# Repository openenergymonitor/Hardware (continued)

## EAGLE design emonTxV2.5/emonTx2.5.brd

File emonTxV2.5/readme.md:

## EmonTx v2.5 Through Hole

**Update: This design was never manufactured or tested**

***

Main features:

- 2x CT sensor inputs using higher quality 3.5mm jacks used on the EmonTx v3 and emontx shield
- 1x ACAC Voltage sensing and power input
- Terminal block power, ADC's and Digital IO breakout + full spare IO breakout.
- Onboard DS18B20 footprint
- Based around ATmega328 + RFM69 core
- Fits in emonTH enclosure

### Eagle schematic and board file

Download both the schematic and board file and open in eagle, click on File > Switch to Board to navigate between schematic view and PCB Board view.

- Schematic: [emonTx2.5.sch](emonTx2.5.sch)
- Board: [emonTx2.5.brd](emonTx2.5.brd)

### Schematic

### Board

### Open Hardware

Hardware designs (schematics and CAD) files are licensed under the [Creative Commons Attribution-ShareAlike 3.0 Unported License](http://creativecommons.org/licenses/by-sa/3.0/) and follow the terms of the [OSHW (Open-source hardware) Statement of Principles 1.0.](http://freedomdefined.org/OSHW)

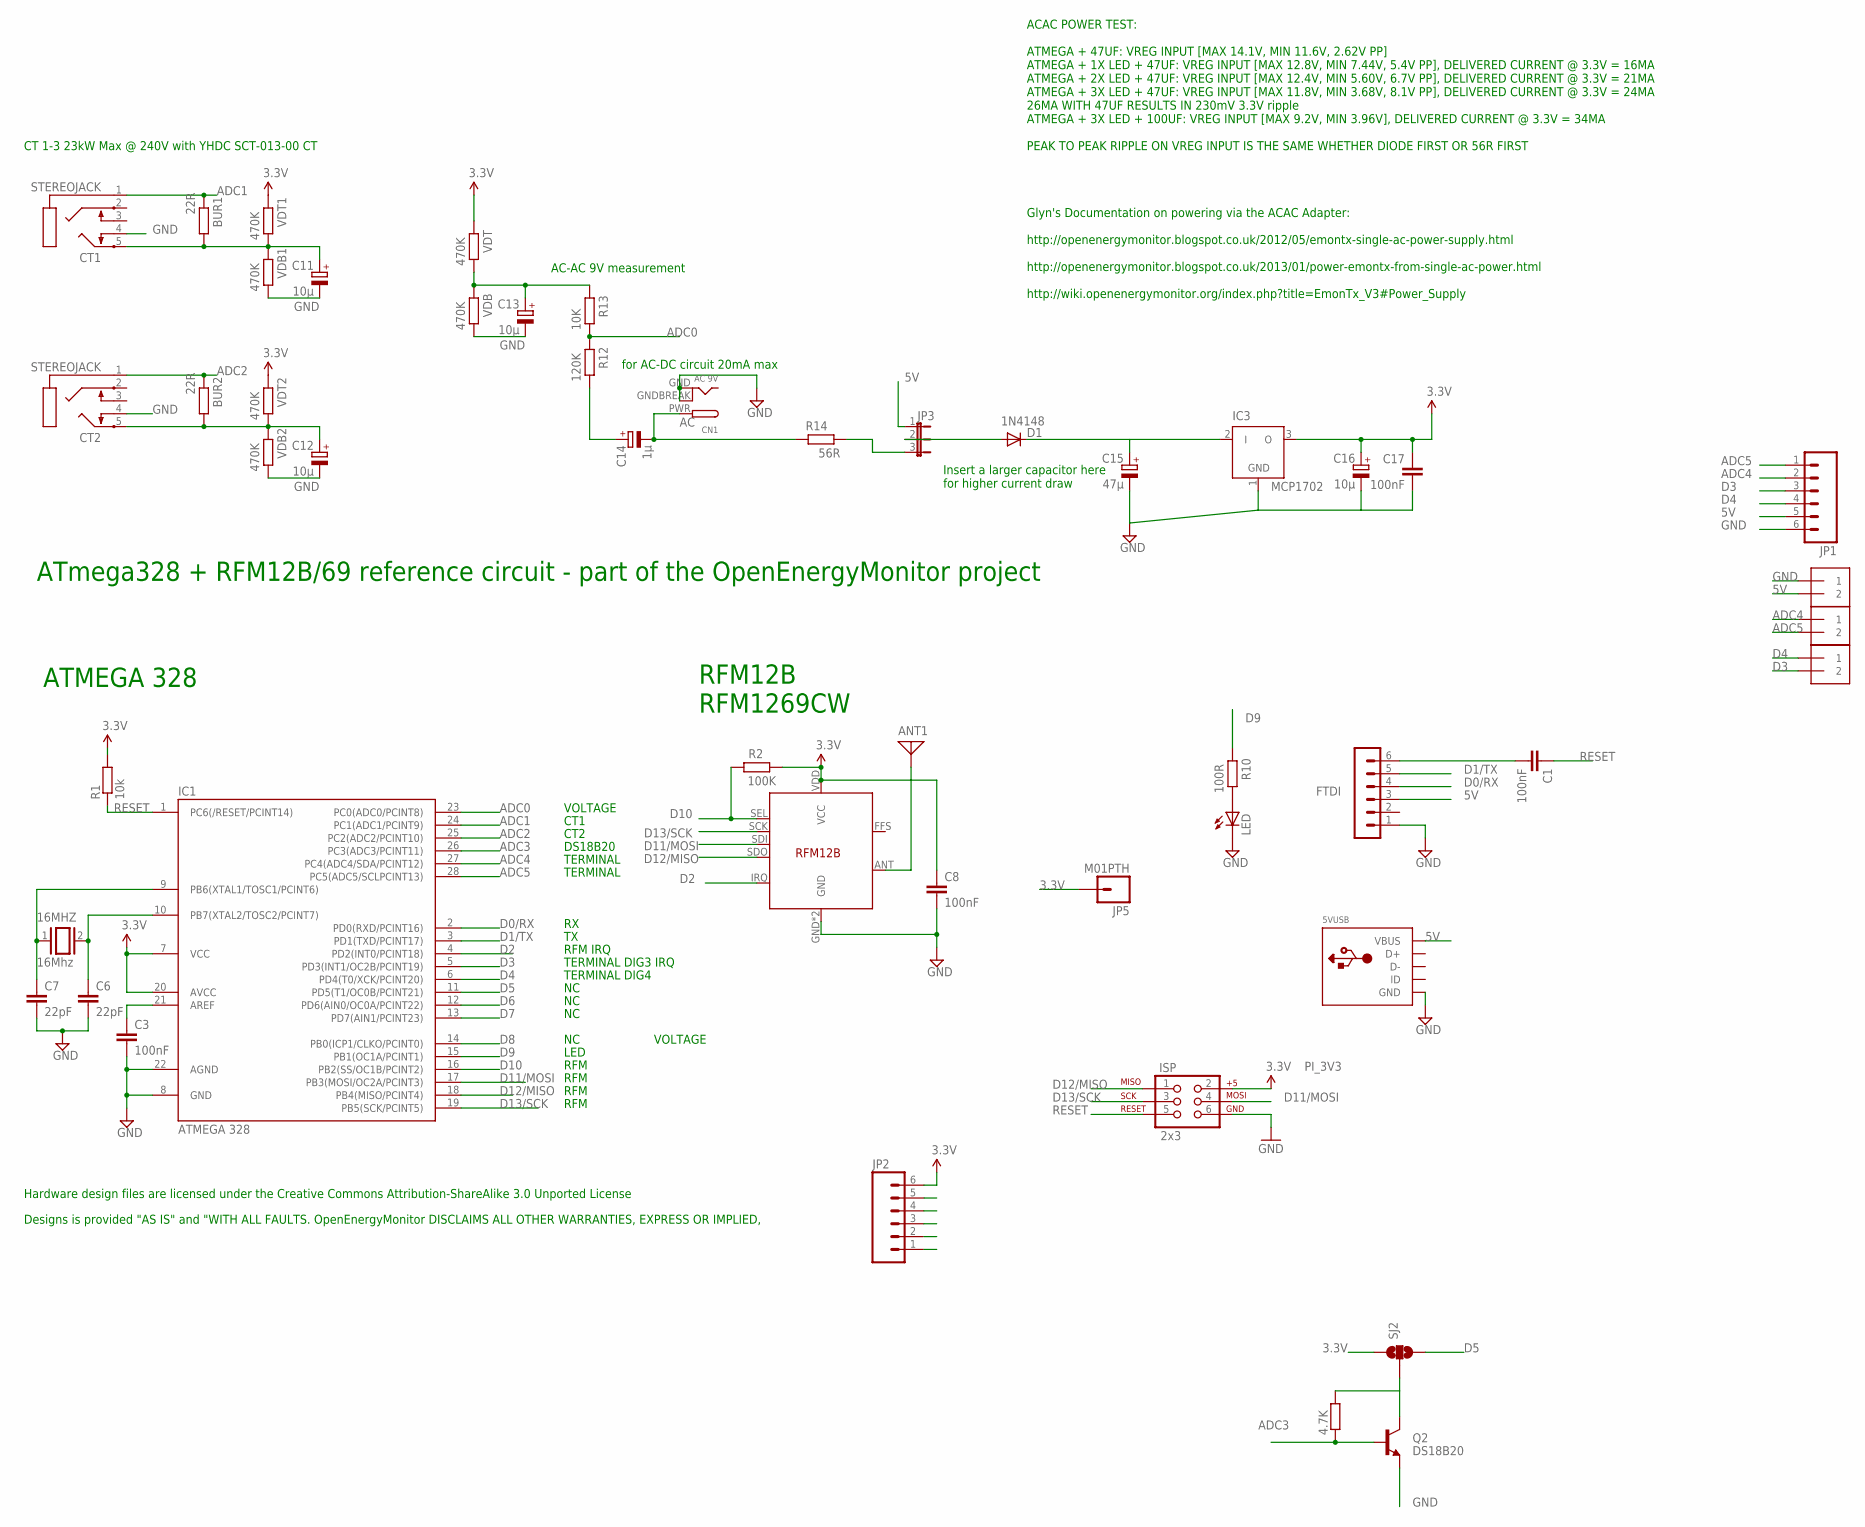
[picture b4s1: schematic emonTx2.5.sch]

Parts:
5VUSB: USBMOLEX; USB-MINIB-THM-MOLEX
16MHZ: 16Mhz; QS
ANT1: ANTENNA; PAD-01
BUR1, BUR2: 22R; 0204/7
C1, C3, C8, C17: 100nF; C025-024X044
C6, C7: 22pF; C2.5-2
C11, C12, C13, C16: 10µ; E1,8-4
C14: 1µ; E1,8-4
C15: 47µ; E1,8-4
CN1: AC 9V; DCJACK_2MM_PTH
CT1, CT2: STEREOJACK; STX3100
D1: 1N4148; DIODE-1N4148
FTDI: FTDI; MA06-1
IC1: ATMEGA 328; DIL28-3
IC3: MCP1702; TO92
ISP: 2x3; 2X3
J1, J2, J3: 1X2-3.5MM
JP1, JP2: M06SIP; 1X06
JP3: JP2E; JP2
JP5: M01PTH; 1X01
LED: LED3MM
Q2: DS18B20; TO-92
R1: 10k; 0204/7
R2: 100K; 0204/7
R9: 4.7K; 0204/7
R10: 100R; 0204/7
R12: 120K; 0204/7
R13: 10K; 0204/7
R14: 56R; 0204/7
SJ2: SOLDERJUMPER_2WAY-OLDS; SJ_3
U$14: RFM12B
VDB, VDB1, VDB2: 470K; 0204/7
VDT, VDT1, VDT2: 470K; 0204/7

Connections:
3.3V: C8.1, C16.+, C17.1, IC1.7 (VCC), IC1.20 (AVCC), IC3.3 (O), ISP.2, JP2.6, JP5.1, R1.2, R2.1, SJ2.1, U$14.VDD (VCC), VDT.2, VDT1.2, VDT2.2
5V: 5VUSB.VBUS, FTDI.3, J3.2, JP1.5, JP3.1
AC: C14.-, CN1.PWR, R14.2
ADC0: IC1.23 (PC0(ADC0/PCINT8)), R12.2, R13.1
ADC1: BUR1.2, CT1.1, IC1.24 (PC1(ADC1/PCINT9))
ADC2: BUR2.2, CT2.1, IC1.25 (PC2(ADC2/PCINT10))
ADC3: IC1.26 (PC3(ADC3/PCINT11)), Q2.2 (B), R9.2
ADC4: IC1.27 (PC4(ADC4/SDA/PCINT12)), J1.1, JP1.2
ADC5: IC1.28 (PC5(ADC5/SCLPCINT13)), J1.2, JP1.1
D0/RX: FTDI.4, IC1.2 (PD0(RXD/PCINT16))
D1/TX: FTDI.5, IC1.3 (PD1(TXD/PCINT17))
D2: IC1.4 (PD2(INT0/PCINT18)), U$14.IRQ
D3: IC1.5 (PD3(INT1/OC2B/PCINT19)), J2.2, JP1.3
D4: IC1.6 (PD4(T0/XCK/PCINT20)), J2.1, JP1.4
D5: IC1.11 (PD5(T1/OC0B/PCINT21)), JP2.2, SJ2.3
D6: IC1.12 (PD6(AIN0/OC0A/PCINT22)), JP2.3
D7: IC1.13 (PD7(AIN1/PCINT23)), JP2.4
D8: IC1.14 (PB0(ICP1/CLKO/PCINT0)), JP2.5
D9: IC1.15 (PB1(OC1A/PCINT1)), R10.2
D10: IC1.16 (PB2(SS/OC1B/PCINT2)), R2.2, U$14.SEL
D11/MOSI: IC1.17 (PB3(MOSI/OC2A/PCINT3)), ISP.4, U$14.SDI
D12/MISO: IC1.18 (PB4(MISO/PCINT4)), ISP.1, U$14.SDO
D13/SCK: IC1.19 (PB5(SCK/PCINT5)), ISP.3, U$14.SCK
DIG1: ANT1.1, U$14.ANT
GND: 5VUSB.GND, C3.2, C6.2, C7.2, C8.2, C11.-, C12.-, C13.-, C15.-, C16.-, C17.2, CN1.GND, CN1.GNDBREAK, CT1.4, CT2.4, FTDI.1, IC1.8 (GND), IC1.22 (AGND), IC3.1 (GND), ISP.6, J3.1, JP1.6, JP2.1, LED.K (C), Q2.1 (E), U$14.GND, U$14.P$12 (GND), VDB.1, VDB1.1, VDB2.1
unnamed: 16MHZ.2, C6.1, IC1.10 (PB7(XTAL2/TOSC2/PCINT7))
unnamed: BUR2.1, C12.+, CT2.5, VDB2.2, VDT2.1
unnamed: JP3.3, R14.1
unnamed: C15.+, D1.C, IC3.2 (I)
unnamed: D1.A, JP3.2
unnamed: C14.+, R12.1
unnamed: LED.A, R10.1
unnamed: Q2.3 (C), R9.1, SJ2.2
unnamed: 16MHZ.1, C7.1, IC1.9 (PB6(XTAL1/TOSC1/PCINT6))
unnamed: C1.2, FTDI.6
unnamed: C3.1, IC1.21 (AREF)
unnamed: C13.+, R13.2, VDB.2, VDT.1
unnamed: BUR1.1, C11.+, CT1.5, VDB1.2, VDT1.1
RESET: C1.1, IC1.1 (PC6(/RESET/PCINT14)), ISP.5, R1.1

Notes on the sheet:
RFM12B RFM1269CW
ATMEGA 328
Hardware design files are licensed under the Creative Commons Attribution-ShareAlike 3.0 Unported License
Designs is provided "AS IS" and "WITH ALL FAULTS. OpenEnergyMonitor DISCLAIMS ALL OTHER WARRANTIES, EXPRESS OR IMPLIED,
ATmega328 + RFM12B/69 reference circuit - part of the OpenEnergyMonitor project
CT 1-3 23kW Max @ 240V with YHDC SCT-013-00 CT
AC-AC 9V measurement
for AC-DC circuit 20mA max
Glyn's Documentation on powering via the ACAC Adapter: http://openenergymonitor.blogspot.co.uk/2012/05/emontx-single-ac-power-supply.html http://openenergymonitor.blogspot.co.uk/2013/01/power-emontx-from-single-ac-power.html http://wiki.openenergymonitor.org/index.php?title=EmonTx_V3#Power_Supply
ACAC POWER TEST: ATMEGA + 47UF: VREG INPUT [MAX 14.1V, MIN 11.6V, 2.62V PP] ATMEGA + 1X LED + 47UF: VREG INPUT [MAX 12.8V, MIN 7.44V, 5.4V PP], DELIVERED CURRENT @ 3.3V = 16MA ATMEGA + 2X LED + 47UF: VREG INPUT [MAX 12.4V, MIN 5.60V, 6.7V PP], DELIVERED CURRENT @ 3.3V = 21MA ATMEGA + 3X LED + 47UF: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
Insert a larger capacitor here for higher current draw
VOLTAGE
CT1
CT2
DS18B20
TERMINAL
RFM IRQ
TERMINAL DIG3 IRQ
TERMINAL DIG4
LED
RFM

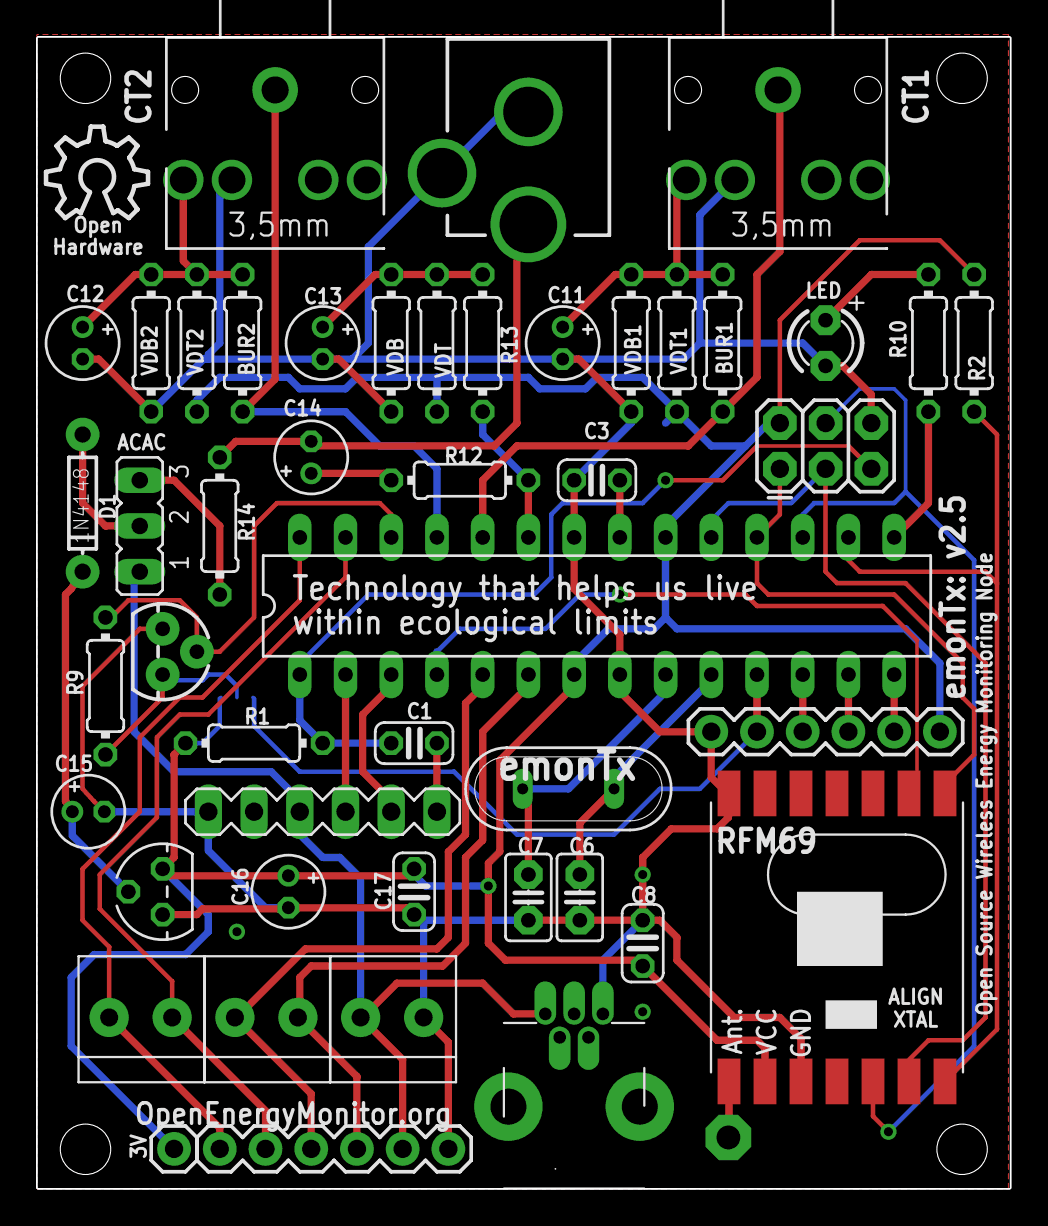
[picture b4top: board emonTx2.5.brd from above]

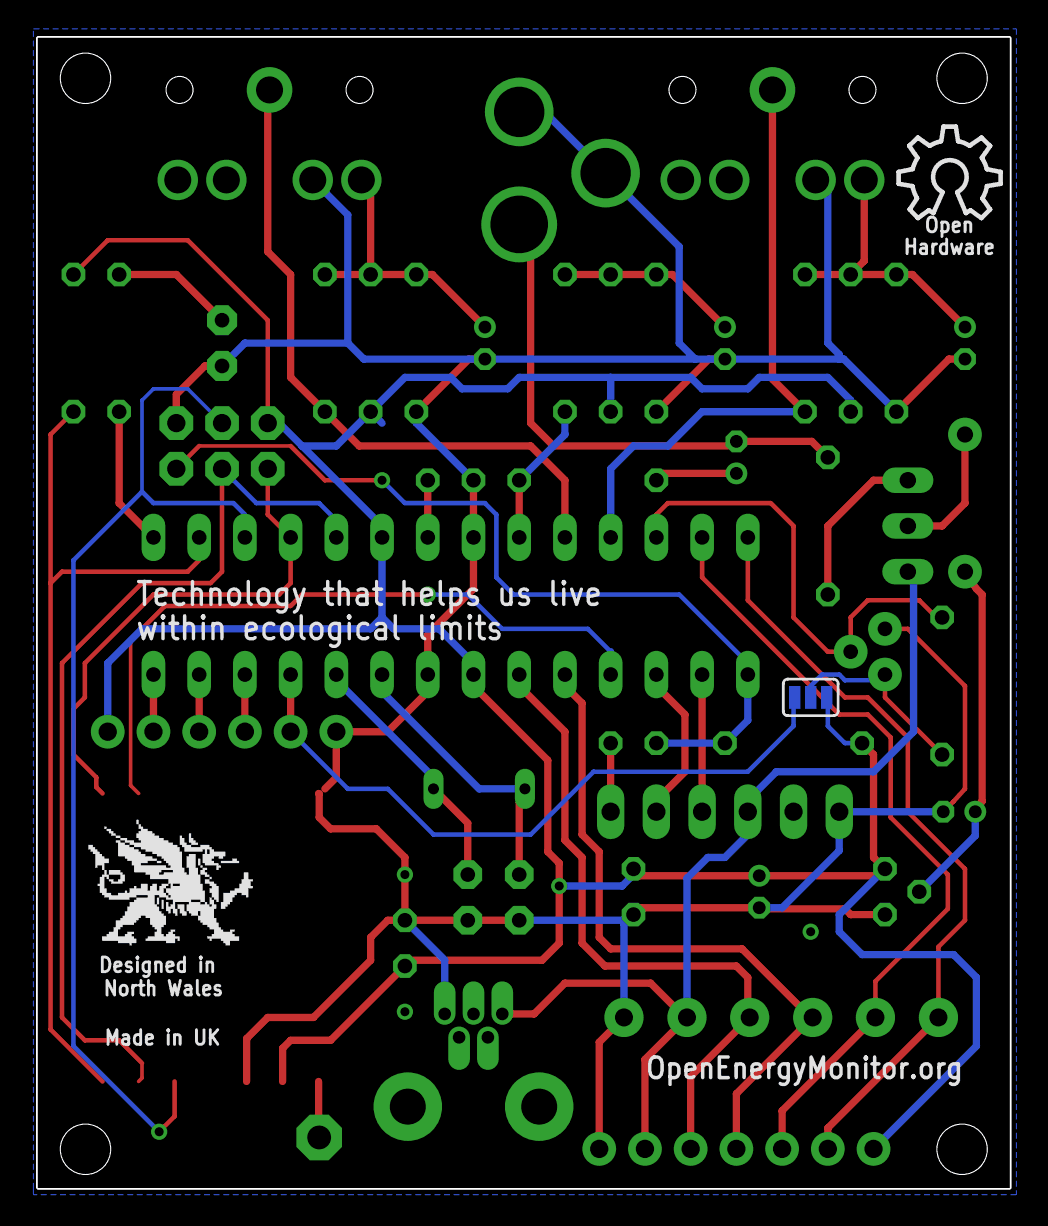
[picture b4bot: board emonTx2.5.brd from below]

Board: 2 copper layers, 54.1 x 64.0 mm, 51 parts (2 on the bottom side), 39 nets.

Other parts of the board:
LOGO1, LOGO2: OSHW_LOGO_10MILX0200-NT; OSHW_10X200_NOTEXT

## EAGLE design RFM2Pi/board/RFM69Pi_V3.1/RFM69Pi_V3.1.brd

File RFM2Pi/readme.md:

## RFM2Pi

A collaboration between Martin Harizanov and OpenEnergyMonitor. Martin's origional repo: https://github.com/mharizanov/RFM2Pi/

### Schematic and board files: 

See board folder

### Schematic

Download schematic: [https://github.com/openenergymonitor/RFM2Pi/blob/master/board/v2/RFM2Pi_v2.6.sch](https://github.com/openenergymonitor/RFM2Pi/blob/master/board/v2/RFM2Pi_v2.6.sch)

### Board

Download board: [https://github.com/openenergymonitor/RFM2Pi/blob/master/board/v2/RFM2Pi_v2.6.brd](https://github.com/openenergymonitor/RFM2Pi/blob/master/board/v2/RFM2Pi_v2.6.brd)

### Open Hardware

Hardware designs (schematics and CAD) files are licensed under the [Creative Commons Attribution-ShareAlike 3.0 Unported License](http://creativecommons.org/licenses/by-sa/3.0/) and follow the terms of the [OSHW (Open-source hardware) Statement of Principles 1.0.](http://freedomdefined.org/OSHW)

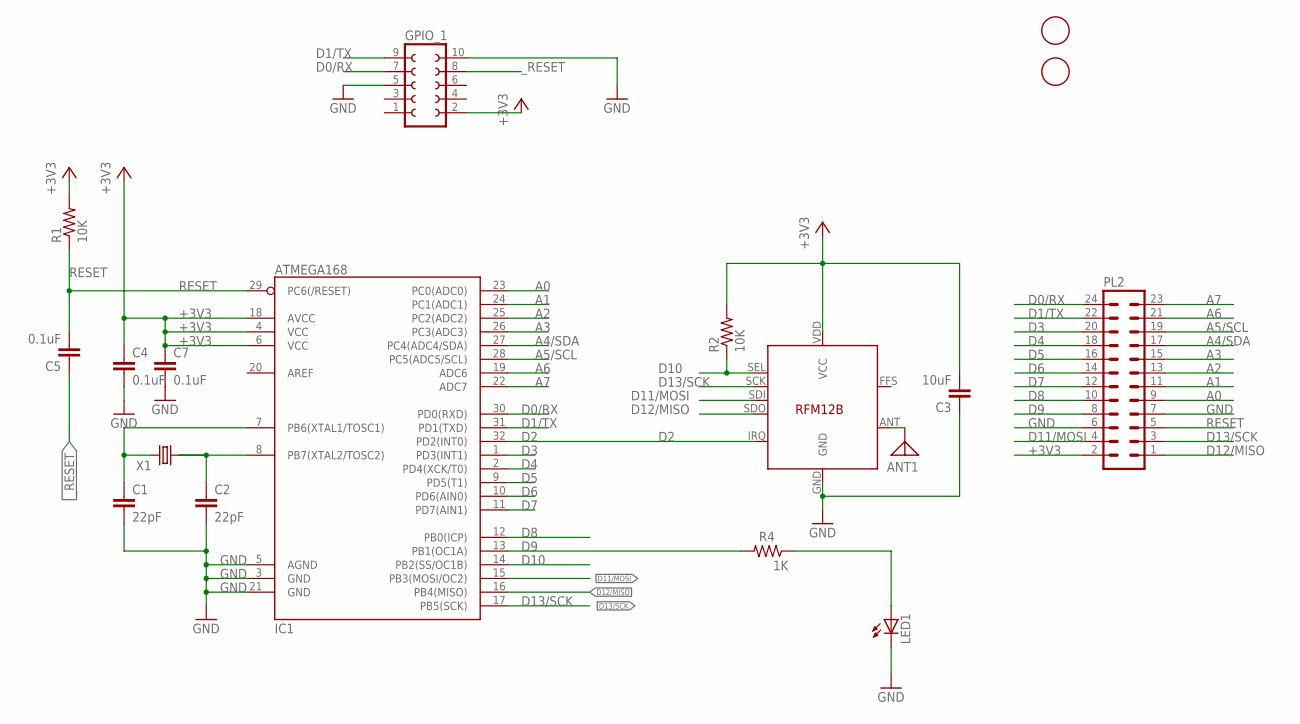
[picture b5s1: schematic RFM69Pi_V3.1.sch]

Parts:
ANT1: ANTENNA; PAD-01
C1, C2: 22pF; C0603
C3: 10uF; C0603
C4, C5, C7: 0.1uF; C0603
GPIO_1: FE05-2
IC1: ATMEGA168; TQFP32-08
LED1: LEDSML0603; SML0603
PL2: MA12-2
R1, R2: 10K; R0603
R4: 1K; R0603
RFM12B-RFM69CW: RFM12B
U$1, U$2: FIDUCIAL; FIDUCIAL_1MM
X1: CRYSTALHC49US; HC49US

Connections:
+3V3: C3.2, C4.1, C7.1, GPIO_1.2, IC1.4 (VCC), IC1.6 (VCC), IC1.18 (AVCC), PL2.2, R1.2, R2.2, RFM12B-RFM69CW.VDD (VCC)
A0: IC1.23 (PC0(ADC0)), PL2.9
A1: IC1.24 (PC1(ADC1)), PL2.11
A2: IC1.25 (PC2(ADC2)), PL2.13
A3: IC1.26 (PC3(ADC3)), PL2.15
A4/SDA: IC1.27 (PC4(ADC4/SDA)), PL2.17
A5/SCL: IC1.28 (PC5(ADC5/SCL)), PL2.19
A6: IC1.19 (ADC6), PL2.21
A7: IC1.22 (ADC7), PL2.23
D0/RX: GPIO_1.7, IC1.30 (PD0(RXD)), PL2.24
D1/TX: GPIO_1.9, IC1.31 (PD1(TXD)), PL2.22
D2: IC1.32 (PD2(INT0)), RFM12B-RFM69CW.IRQ
D3: IC1.1 (PD3(INT1)), PL2.20
D4: IC1.2 (PD4(XCK/T0)), PL2.18
D5: IC1.9 (PD5(T1)), PL2.16
D6: IC1.10 (PD6(AIN0)), PL2.14
D7: IC1.11 (PD7(AIN1)), PL2.12
D8: IC1.12 (PB0(ICP)), PL2.10
D9: IC1.13 (PB1(OC1A)), PL2.8, R4.2
D10: IC1.14 (PB2(SS/OC1B)), R2.1, RFM12B-RFM69CW.SEL
D11/MOSI: IC1.15 (PB3(MOSI/OC2)), PL2.4, RFM12B-RFM69CW.SDI
D12/MISO: IC1.16 (PB4(MISO)), PL2.1, RFM12B-RFM69CW.SDO
D13/SCK: IC1.17 (PB5(SCK)), PL2.3, RFM12B-RFM69CW.SCK
GND: C1.2, C2.2, C3.1, C4.2, C7.2, GPIO_1.5, GPIO_1.10, IC1.3 (GND), IC1.5 (AGND), IC1.21 (GND), LED1.C, PL2.6, PL2.7, RFM12B-RFM69CW.GND
unnamed: C1.1, IC1.7 (PB6(XTAL1/TOSC1)), X1.2
unnamed: C2.1, IC1.8 (PB7(XTAL2/TOSC2)), X1.1
unnamed: LED1.A, R4.1
unnamed: ANT1.1, RFM12B-RFM69CW.ANT
RESET: C5.2, IC1.29 (PC6(/RESET)), PL2.5, R1.1
_RESET: C5.1, GPIO_1.8

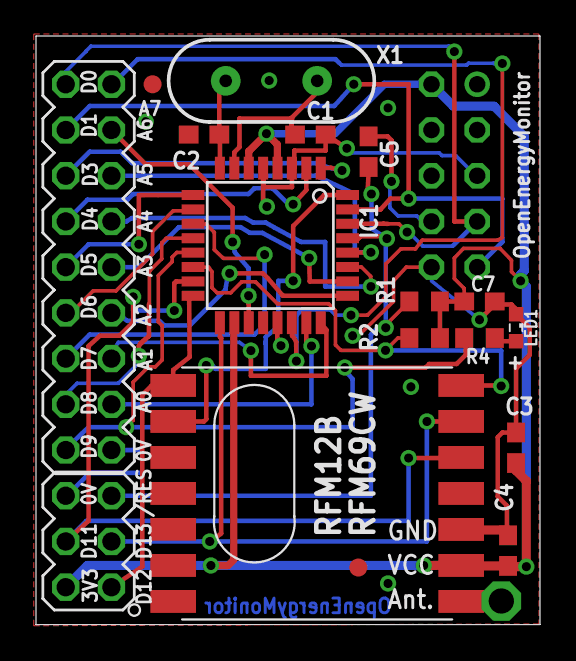
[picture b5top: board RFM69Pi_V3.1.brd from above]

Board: 2 copper layers, 28.0 x 32.7 mm, 18 parts (0 on the bottom side), 30 nets.

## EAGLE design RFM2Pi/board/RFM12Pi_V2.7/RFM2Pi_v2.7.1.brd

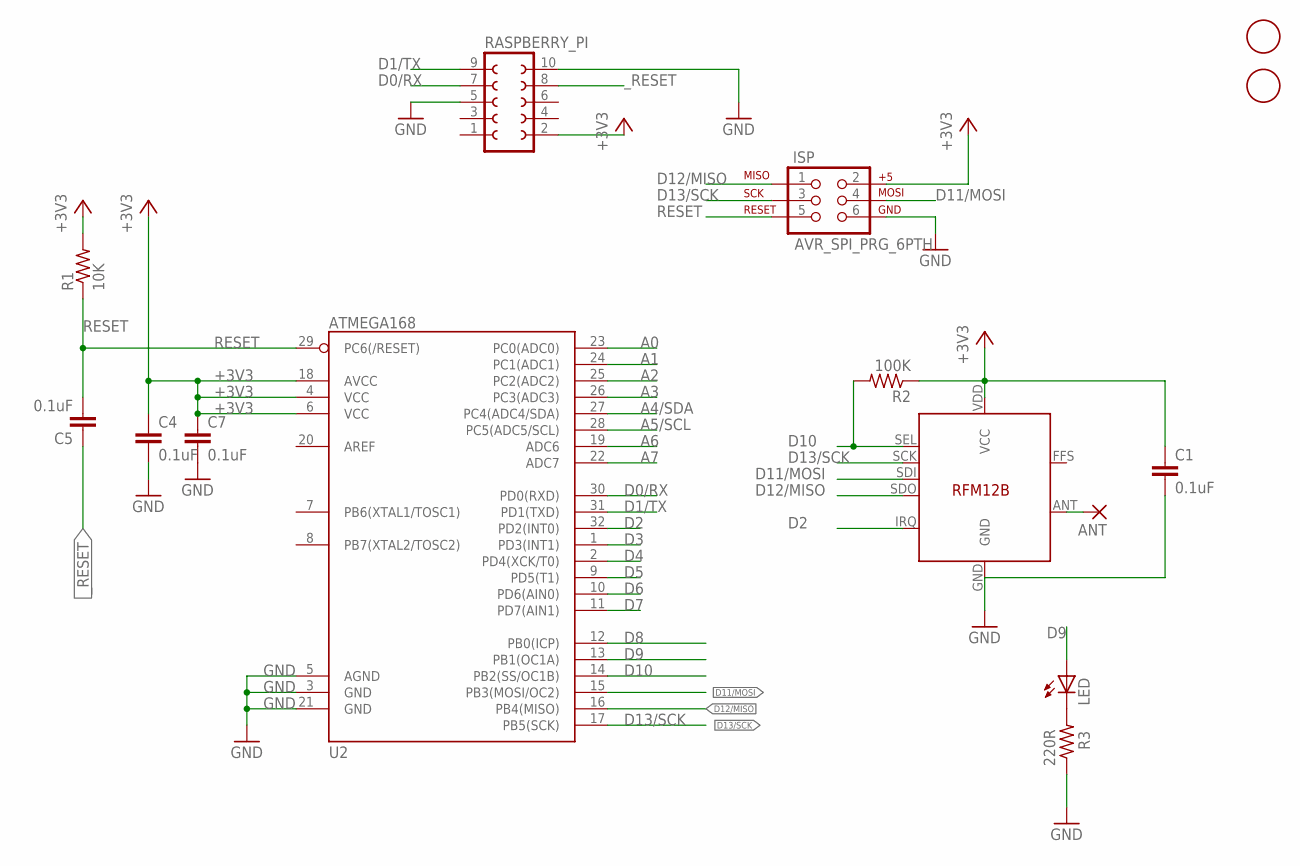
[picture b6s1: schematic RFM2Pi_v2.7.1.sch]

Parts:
ANT: 1,6/0,8
C1, C4, C5, C7: 0.1uF; C0603
ISP: AVR_SPI_PRG_6PTH; 2X3
LED: LEDSML0603; SML0603
R1: 10K; R0603
R2: 100K; R0603
R3: 220R; R0603
RASPBERRY_PI: FE05-2
RFM12B: RFM12B
U2: ATMEGA168; TQFP32-08
U$1, U$2: FIDUCIAL; FIDUCIAL_1MM

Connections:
+3V3: C1.1, C4.1, C7.1, ISP.2, R1.2, R2.1, RASPBERRY_PI.2, RFM12B.VDD (VCC), U2.4 (VCC), U2.6 (VCC), U2.18 (AVCC)
A0: U2.23 (PC0(ADC0))
A1: U2.24 (PC1(ADC1))
A2: U2.25 (PC2(ADC2))
A3: U2.26 (PC3(ADC3))
A4/SDA: U2.27 (PC4(ADC4/SDA))
A5/SCL: U2.28 (PC5(ADC5/SCL))
A6: U2.19 (ADC6)
A7: U2.22 (ADC7)
D0/RX: RASPBERRY_PI.7, U2.30 (PD0(RXD))
D1/TX: RASPBERRY_PI.9, U2.31 (PD1(TXD))
D2: RFM12B.IRQ, U2.32 (PD2(INT0))
D3: U2.1 (PD3(INT1))
D4: U2.2 (PD4(XCK/T0))
D5: U2.9 (PD5(T1))
D6: U2.10 (PD6(AIN0))
D7: U2.11 (PD7(AIN1))
D8: U2.12 (PB0(ICP))
D9: LED.A, U2.13 (PB1(OC1A))
D10: R2.2, RFM12B.SEL, U2.14 (PB2(SS/OC1B))
D11/MOSI: ISP.4, RFM12B.SDI, U2.15 (PB3(MOSI/OC2))
D12/MISO: ISP.1, RFM12B.SDO, U2.16 (PB4(MISO))
D13/SCK: ISP.3, RFM12B.SCK, U2.17 (PB5(SCK))
GND: C1.2, C4.2, C7.2, ISP.6, R3.1, RASPBERRY_PI.5, RASPBERRY_PI.10, RFM12B.GND, U2.3 (GND), U2.5 (AGND), U2.21 (GND)
unnamed: LED.C, R3.2
unnamed: ANT.1, RFM12B.ANT
RESET: C5.2, ISP.5, R1.1, U2.29 (PC6(/RESET))
_RESET: C5.1, RASPBERRY_PI.8

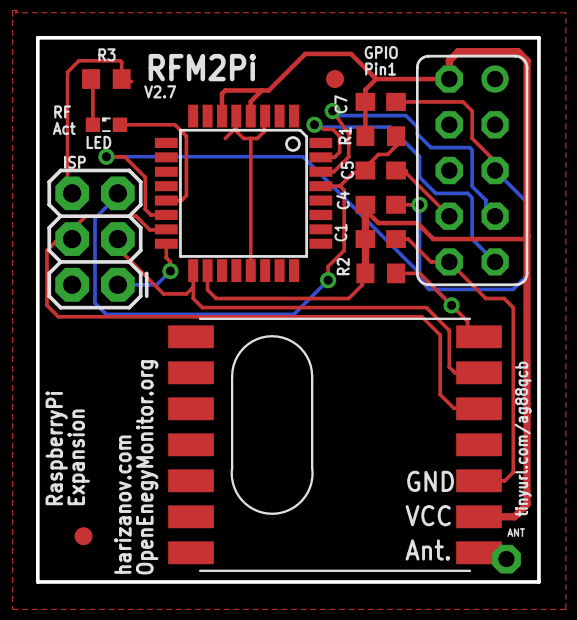
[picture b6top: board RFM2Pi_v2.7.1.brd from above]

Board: 2 copper layers, 27.8 x 30.2 mm, 15 parts (0 on the bottom side), 14 nets.

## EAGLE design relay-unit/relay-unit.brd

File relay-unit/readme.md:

## Very early concept for a in-line plug energy monitor plus integrated relay for switching an appliance or plug bank on/off.

**Note:** This is an untested design in the early stages of development and involves high voltages on the board. If you use this design please ensure you independently check its suitability and safety.

***

### Atmega through-hole version

Download schematic: [relay-unit.sch](relay-unit.sch)

Download board file: [relay-unit.brd](relay-unit.brd)

### IET Socket's and CT

### Open Hardware

Hardware designs (schematics and CAD) files are licensed under the [Creative Commons Attribution-ShareAlike 3.0 Unported License](http://creativecommons.org/licenses/by-sa/3.0/) and follow the terms of the [OSHW (Open-source hardware) Statement of Principles 1.0.](http://freedomdefined.org/OSHW)

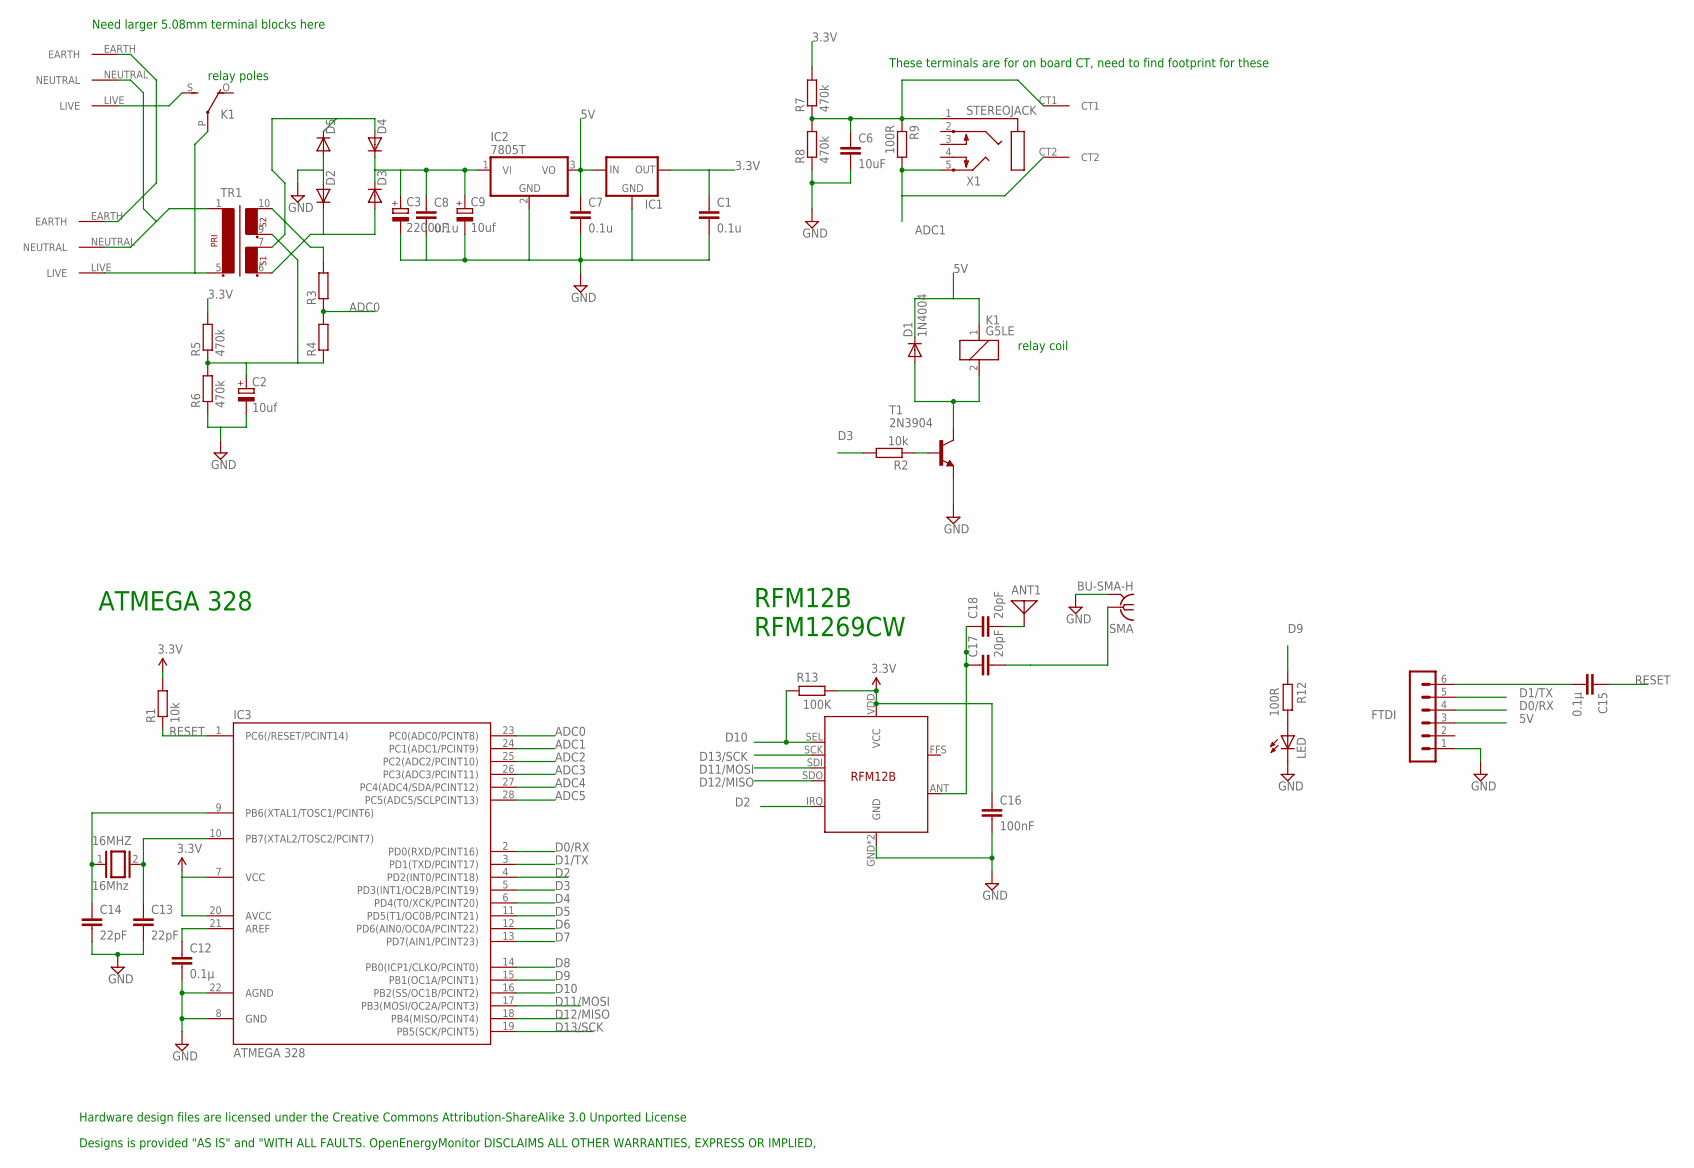
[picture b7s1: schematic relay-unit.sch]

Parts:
16MHZ: 16Mhz; QS
ANT1: ANTENNA; PAD-01
C1, C7, C8: 0.1u; C025-024X044
C2, C9: 10uf; E1,8-4
C3: 2200uF; E5-13
C6: 10uF; C025-024X044
C12, C15: 0.1µ; C025-024X044
C13, C14: 22pF; C2.5-2
C16: 100nF; C025-024X044
C17, C18: 20pF; C025-024X044
D1, D2, D3, D4, D5: 1N4004; DO41-10
FTDI: FTDI; MA06-1
IC1: MCP1700TRI; TO92
IC2: 7805T; TO220H
IC3: ATMEGA 328; DIL28-3
K1: G5LE
LED: LED3MM
R1, R2: 10k; 0204/7
R3, R4: R-EU_0204/7; 0204/7
R5, R6, R7, R8: 470k; 0204/7
R9, R12: 100R; 0204/7
R13: 100K; 0204/7
SMA: BU-SMA-H
T1: 2N3904; TO92
TR1: EI30-2
U$1: TESTTEST; TEST
U$2: AC_IN
U$3: CT
U$14: RFM12B
X1: STEREOJACK; STX3100

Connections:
3.3V: C1.1, C16.1, IC1.3 (OUT), IC3.7 (VCC), IC3.20 (AVCC), R1.2, R5.2, R7.2, R13.1, U$14.VDD (VCC)
5V: C7.1, D1.C, FTDI.3, IC1.2 (IN), IC2.3 (VO), K1.1
ADC0: IC3.23 (PC0(ADC0/PCINT8)), R3.1, R4.2
ADC1: IC3.24 (PC1(ADC1/PCINT9)), R9.2, U$3.CT2, X1.5
ADC2: IC3.25 (PC2(ADC2/PCINT10))
ADC3: IC3.26 (PC3(ADC3/PCINT11))
ADC4: IC3.27 (PC4(ADC4/SDA/PCINT12))
ADC5: IC3.28 (PC5(ADC5/SCLPCINT13))
D0/RX: FTDI.4, IC3.2 (PD0(RXD/PCINT16))
D1/TX: FTDI.5, IC3.3 (PD1(TXD/PCINT17))
D2: IC3.4 (PD2(INT0/PCINT18)), U$14.IRQ
D3: IC3.5 (PD3(INT1/OC2B/PCINT19)), R2.2
D4: IC3.6 (PD4(T0/XCK/PCINT20))
D5: IC3.11 (PD5(T1/OC0B/PCINT21))
D6: IC3.12 (PD6(AIN0/OC0A/PCINT22))
D7: IC3.13 (PD7(AIN1/PCINT23))
D8: IC3.14 (PB0(ICP1/CLKO/PCINT0))
D9: IC3.15 (PB1(OC1A/PCINT1)), R12.2
D10: IC3.16 (PB2(SS/OC1B/PCINT2)), R13.2, U$14.SEL
D11/MOSI: IC3.17 (PB3(MOSI/OC2A/PCINT3)), U$14.SDI
D12/MISO: IC3.18 (PB4(MISO/PCINT4)), U$14.SDO
D13/SCK: IC3.19 (PB5(SCK/PCINT5)), U$14.SCK
DIG1: C17.1, C18.1, U$14.ANT
GND: C1.2, C2.-, C3.-, C6.2, C7.2, C8.2, C9.-, C12.2, C13.2, C14.2, C16.2, D2.A, D5.A, FTDI.1, IC1.1 (GND), IC2.2 (GND), IC3.8 (GND), IC3.22 (AGND), LED.K (C), R6.1, R8.1, SMA.2, SMA.3 (2), SMA.4 (2), SMA.5 (2), T1.3 (E), U$14.GND, U$14.P$12 (GND)
unnamed: C12.1, IC3.21 (AREF)
unnamed: 16MHZ.2, C13.1, IC3.10 (PB7(XTAL2/TOSC2/PCINT7))
unnamed: C15.2, FTDI.6
unnamed: LED.A, R12.1
unnamed: ANT1.1, C18.2
unnamed: 16MHZ.1, C14.1, IC3.9 (PB6(XTAL1/TOSC1/PCINT6))
unnamed: C3.+, C8.1, C9.+, D3.C, D4.C, IC2.1 (VI)
unnamed: R3.2, TR1.10 (6)
unnamed: R2.1, T1.2 (B)
unnamed: D1.A, K1.2, T1.1 (C)
unnamed: K1.S, U$1.LIVE
unnamed: TR1.1, U$1.NEUTRAL, U$2.NEUTRAL
unnamed: C2.+, R4.1, R5.1, R6.2, TR1.9 (5)
unnamed: D2.C, D3.A, TR1.6 (3)
unnamed: C17.2, SMA.1
unnamed: C6.1, R7.1, R8.2, R9.1, U$3.CT1, X1.1
unnamed: D4.A, D5.C, TR1.7 (4)
unnamed: U$1.EARTH, U$2.EARTH
unnamed: K1.P, TR1.5 (2), U$2.LIVE
RESET: C15.1, IC3.1 (PC6(/RESET/PCINT14)), R1.1

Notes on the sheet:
Need larger 5.08mm terminal blocks here
These terminals are for on board CT, need to find footprint for these
relay coil
relay poles
RFM12B RFM1269CW
ATMEGA 328
Hardware design files are licensed under the Creative Commons Attribution-ShareAlike 3.0 Unported License
Designs is provided "AS IS" and "WITH ALL FAULTS. OpenEnergyMonitor DISCLAIMS ALL OTHER WARRANTIES, EXPRESS OR IMPLIED,

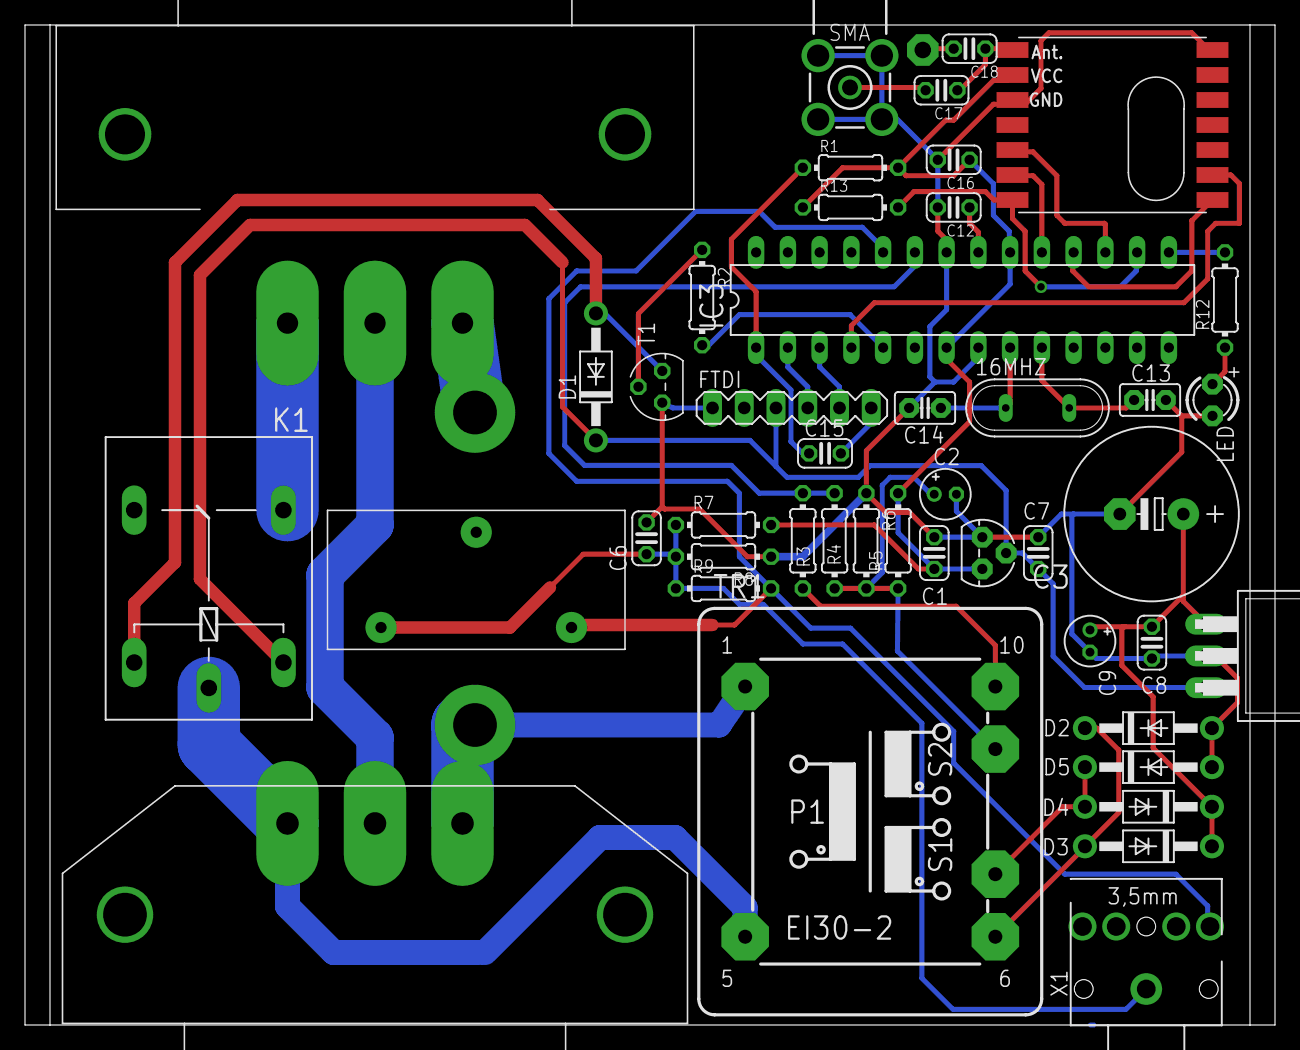
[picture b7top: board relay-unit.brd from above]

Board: 2 copper layers, 100.0 x 80.0 mm, 46 parts (0 on the bottom side), 35 nets.

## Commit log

2014-08-20 Initial readme
2014-08-20 formatting
2014-08-20 12 input pulse counter files
2014-08-20 EmonTx Shield SMT
2014-08-20 in development energy monitor + relay unit
2014-08-20 RFM2Pi schmatic and board image
2014-08-21 add emonTx, emonGLCD designs
2014-08-21 add new emonGLCD V1.5
2014-08-21 EmonTH and EmonTx shield v1 files
2014-08-21 open hardware logo
2014-08-21 IETSockets and CT image
2014-09-03 Development helpers
2014-09-03 Throughhole Atmega + RFM69 base example
2014-09-03 Rename
2014-09-03 Initial concept of updated through-hole emontx with powered by ACAC + 2 CT's fitting in EmonTH case.
2014-09-03 readme for emontx through-hole concept
2014-09-03 Updated relay-unit with atmega328 and rfm12/69
2014-09-03 New relay-unit design and old designs archived
2014-09-04 Single voltage regulator, power supply test results, usb positioning
2014-10-27 add RFM12Pi hardware
2014-10-27 edit rfm12pi readme
2014-10-27 edit readme
2014-10-29 RFM12Pi V2.7 revision compleate using kicad
2014-10-31 add rfm12pi v2.7 bom
2014-11-07 fix rfm12pi v2.6
2014-11-13 update kicad and remove rfm12ppi frmware, see openenergymonitor/rfm12pi repo for latest firmware
2014-12-08 add emonTx V3.4 files
2014-12-08 organise folders
2014-12-08 add readme for root folder
2015-02-06 add RFM12Pi V3.1
2015-02-06 add V3.1 readme
2015-02-06 update readme wth v3.1 images
2015-02-06 typo
2015-02-09 photos
2015-02-10 Add Ken credit
2015-02-28 add emonTx V3.4 BOM
2015-03-16 add emonPi and new emonTH
2015-04-28 add emonPi case CAD drawing with dimentions
2015-04-28 add .png drawing cad
2015-05-22 emontx throughhole 2
2015-06-01 Embodied energy analysis for the emonpi 1st draft
2015-06-06 EmonTx v2.5 design
2015-07-25 add emonPi V1.6
2015-11-24 add emonPi V1.6 board assembled photo
2015-11-24 resize photo
2015-11-26 add low res photo
2015-12-18 Heatpump Monitor hardware schematic and board file
2016-03-07 Introduce set of gitignore rules
    Combined together
    Eagle specific https://github.com/github/gitignore/blob/master/Eagle.gitignore
    and OSX specific https://github.com/github/gitignore/blob/master/Global/OSX.gitignore
2016-03-07 Removed backup copy of readmy.md files
2016-03-18 add emonTx V3.4.1 design
2016-07-27 emonTH V2.0 prototype
2016-07-28 add emonth v2.0.1 led footprint update
2016-08-19 emonTH gerbers
2016-08-19 add emonTx V3.4.2 & change log
2016-08-19 readme
2016-08-19 add export
2017-01-14 move emonglcd hardware to emonglcd repo
2017-02-27 update docs URL
2017-03-10 move hardware to dedicated repos
2019-01-21 https://github.com/decentralizedbloodbank/OpenLog
    https://github.com/decentralizedbloodbank/OpenLog
